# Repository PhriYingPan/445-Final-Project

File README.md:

# Desk Aid Learning Device 

### Team Members

- [Aidan Johnston](https://github.com/AidanJ16)
- [Conan Pan](https://github.com/PhriYingPan)
- [Ethan Ge](https://github.com/ethange2)

## 1.1 Problem

In recent years, there has been a growing trend of integrating technology into schools. This trend has been accelerated by the lasting impacts of the Covid-19 pandemic and the continuous advancements in digital devices and tools. Schools across the nation have adopted computers, tablets, and virtual learning platforms to enhance education and increase accessibility in the pursuit of modernizing the classroom. While these technologies offer incredible benefits, they also introduce challenges, particularly in elementary school classrooms. 

One of the most critical problems is the effect screen time is having on students. By incorporating technological devices in classrooms, students are spreading prolonged periods interacting with screens. Studies have begun to highlight how this excessive screen time can lead to a severe lack of social skills, shorter attention spans, and higher frequencies of disruptions. These trends contribute to a less effective and unhealthy learning environment. Furthermore, studies are exploring connections between prolonged exposure to screens and decreases in mental and physical well-being. Therefore, in the pursuit of generating a more social, engaging, and nurturing environment for young students we propose the desk learning aid device.

## 1.2 Solution

The desk learning aid device will function through various buttons and a scroller connected to a customized PCB device. These buttons and the scroller will correspond to responding to polls/questions, comprehension checks, asking questions, and more. The device will communicate to an application that can be monitored by the teacher where they will receive real-time feedback. The teacher can have a better understanding of the student’s comprehension levels and be able to properly cater towards providing the students the most effective lesson. The purpose of this device would be to provide a cost-effective solution that can be set up at each student’s desk to promote a stronger and healthier learning environment for students. This differs from other options on the market due to easier set up because other options require you to create a question in order to receive a response, however, our device allows for many passive inputs including comprehension and other urgent needs. In addition, other portable solutions require students to buy each device individually costing them hundreds of dollars, but our solution only requires the purchase of a reusable RFID keycard that is cheap and easy to use.

# Visual Aid 

# Results

 - [Demo Video](https://drive.google.com/file/d/13fJDIUi9QKVj2l2KASiBSuiVs_a9EkWj/view?usp=sharing)
 - [Presentation](https://github.com/user-attachments/files/20017662/Desk.Aid.Learning.Device.Team.27.pptx)
 - [Design Document](https://github.com/user-attachments/files/20017668/445.Design.Document.3.pdf)

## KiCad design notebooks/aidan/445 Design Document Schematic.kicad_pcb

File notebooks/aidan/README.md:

# Aidan Johnston's Lab Notebook – Desk Learning Aid Device

This notebook documents the comprehensive design, development, testing, and firmware implementation for the Desk Learning Aid Device. It particularly highlights my contributions to the customized PCB and subsystem integration.

---

## 2025-02-01 – Initial Project Direction

**Objectives:**

* Discussed the core project idea and goals with teammates and our TA, Kaiwen Cao.
* Explored engagement mechanisms suitable for classroom environments that avoid excessive screen time.

**Progress:**

* Proposed using a physical interaction system incorporating RFID-based student identification, button-based input, and a rotary encoder or potentiometer scroller.
* Envisioned a backend system supported by Firebase to relay data to a real-time web dashboard accessible to teachers.
* Sketched an initial block diagram representing all subsystems (power, microcontroller, interface, input, and RFID).

---

## 2025-02-14 – Finalize Project

**Objectives:**

* Solidify the overall architecture and prepare for the proposal review.

**Progress:**

* Finalized a refined block diagram detailing subsystem interactions.
* Designed initial device enclosures and mounting plans for discussion with the Machine Shop.
* Scheduled zoom meetings with elementary school teachers to ensure project alignment with classroom needs.
* Began outlining our project proposal for review by course instructors and TAs.

---

## 2025-02-23 – Initial PCB Design Part 1

**Objectives:**

* Begin translating conceptual design into manufacturable electronic schematics.

**Progress:**

* Created a rough draft schematic in KiCad featuring major components: ESP32-S3, push buttons, RFID, voltage regulators, and display interface.
* Assigned preliminary footprints to each component, focusing on pin mapping and layout constraints.

---

## 2025-03-05 – Initial PCB Design Part 2

**Objectives:**

* Convert schematic to a routed PCB design and initiate documentation.

**Progress:**

* Structured the PCB by subsystem (power, input, interface, RFID, microcontroller), allowing for intuitive routing.
* Assigned logical labels, visibility settings, and ground stitching to reduce EMI.
* Helped draft the design documentation section related to PCB layout, component selection, and routing decisions.

---

## 2025-03-13 – Initial PCB Design Part 3

**Objectives:**

* Submit the initial board to PCBWay.

**Progress:**

* Used KiCad's Design Rule Checker to identify and correct errors.
* Submitted and passed PCBWay's manufacturing audit.
* Submitted the design to our TA as apart of the Second Round Orders.

---

## 2025-03-24 – Updated PCB Design Part 1

**Objectives:**

* Evaluate prior board and fix discovered issues.

**Challenges:**

* Incorrect footprint for buck-boost converter (TPS63001).
* Programming circuit for ESP32-S3 not compatible with UART flashing.
* Incorrect footprints for push buttons, inverters, and LCD connector.

**Solutions:**

* Corrected all footprints by referencing datasheets and comparing to KiCad libraries.
* Revised programming method to use USB-to-UART dongle with GND, TX, RX, DTR, RTS lines.
* Rechecked layout and connections for consistency and ease of access.

---

## 2025-03-31 – Updated PCB Design Part 2

**Objectives:**

* Submit improved board design.

**Progress:**

* Rerouted traces and updated board labeling.
* Verified footprint clearances and pad sizes.
* Used KiCad's Design Rule Checker to identify and correct errors.
* Submitted and passed PCBWay's manufacturing audit.
* Submitted the design to our TA as apart of the Third Round Orders.

---

## 2025-04-17 – Hardware Testing

**Objectives:**

* Validate the power subsystem and ESP32 flashing.

**Progress:**

* Measured 3.27V at ESP32 input pin (target: 3.3V).
* Identified error in design: resistor R13 (pull-down) interfered with programming, removed it to enable successful flashing.

---

## 2025-04-29 – Software Testing

**Objectives:**

* Program LCD to verify interface subsystem.

**Progress:**

* Initial attempts to display characters failed.
* Identified reversed SPI pin assignments to LCD: MOSI needed to connect to SID, and MISO to SOD.
* Recognized need for external RST circuit for reliable LCD initialization.

---
## Verification Procedures

**1. DRC Testing**

* All boards verified using KiCad’s DRC.
* Ensured clearance, trace width, and via rules met manufacturing constraints.

**2. Continuity Testing**

* Verified pin-to-pin connections and ground continuity.
* Used multimeter beep function across all critical signal lines.

**3. Power Integrity Test**

* Verified output voltages at ESP32 (3.27V), LCD, and RFID reader.
* Measured battery charge and boost output stability under load.

**4. Boot and Flash Test**

* Helped successfully flash test program using esptool.py.

**5. Input Test**

* Button presses triggered correct GPIO interrupts.
* Potentiometer yielded stable ADC values.

---

## Bibliographic References

1. Espressif Systems. (2023). *ESP32-S3-WROOM-1 & ESP32-S3-WROOM-1U Datasheet*.
2. Firebase. (2024). *Realtime Database Documentation*.
3. ELECTRONIC ASSEMBLY GmbH. (n.d.). *DOGS104E Graphic Display Module*.
4. Texas Instruments. (2008). *TPS63000 High-Efficiency Buck-Boost Converter Datasheet*.
5. TOPPOWER. (2023). *TP4057 Battery Charging and Protection IC Datasheet*.
6. Texas Instruments. (2002). *SN74LS05 Hex Inverter Datasheet*.
7. NXP Semiconductors. (2018). *PN512 NFC Reader IC Datasheet*.
8. Adafruit. (n.d.). *Push Button #492*.
9. Bourns Inc. (2020). *PDB181 Series Potentiometer Datasheet*.
10. IEEE. (2023). *IEEE Code of Ethics*.
11. U8G2 Library Documentation. (2024). *Monochrome Graphics Library for Embedded Devices*.

---

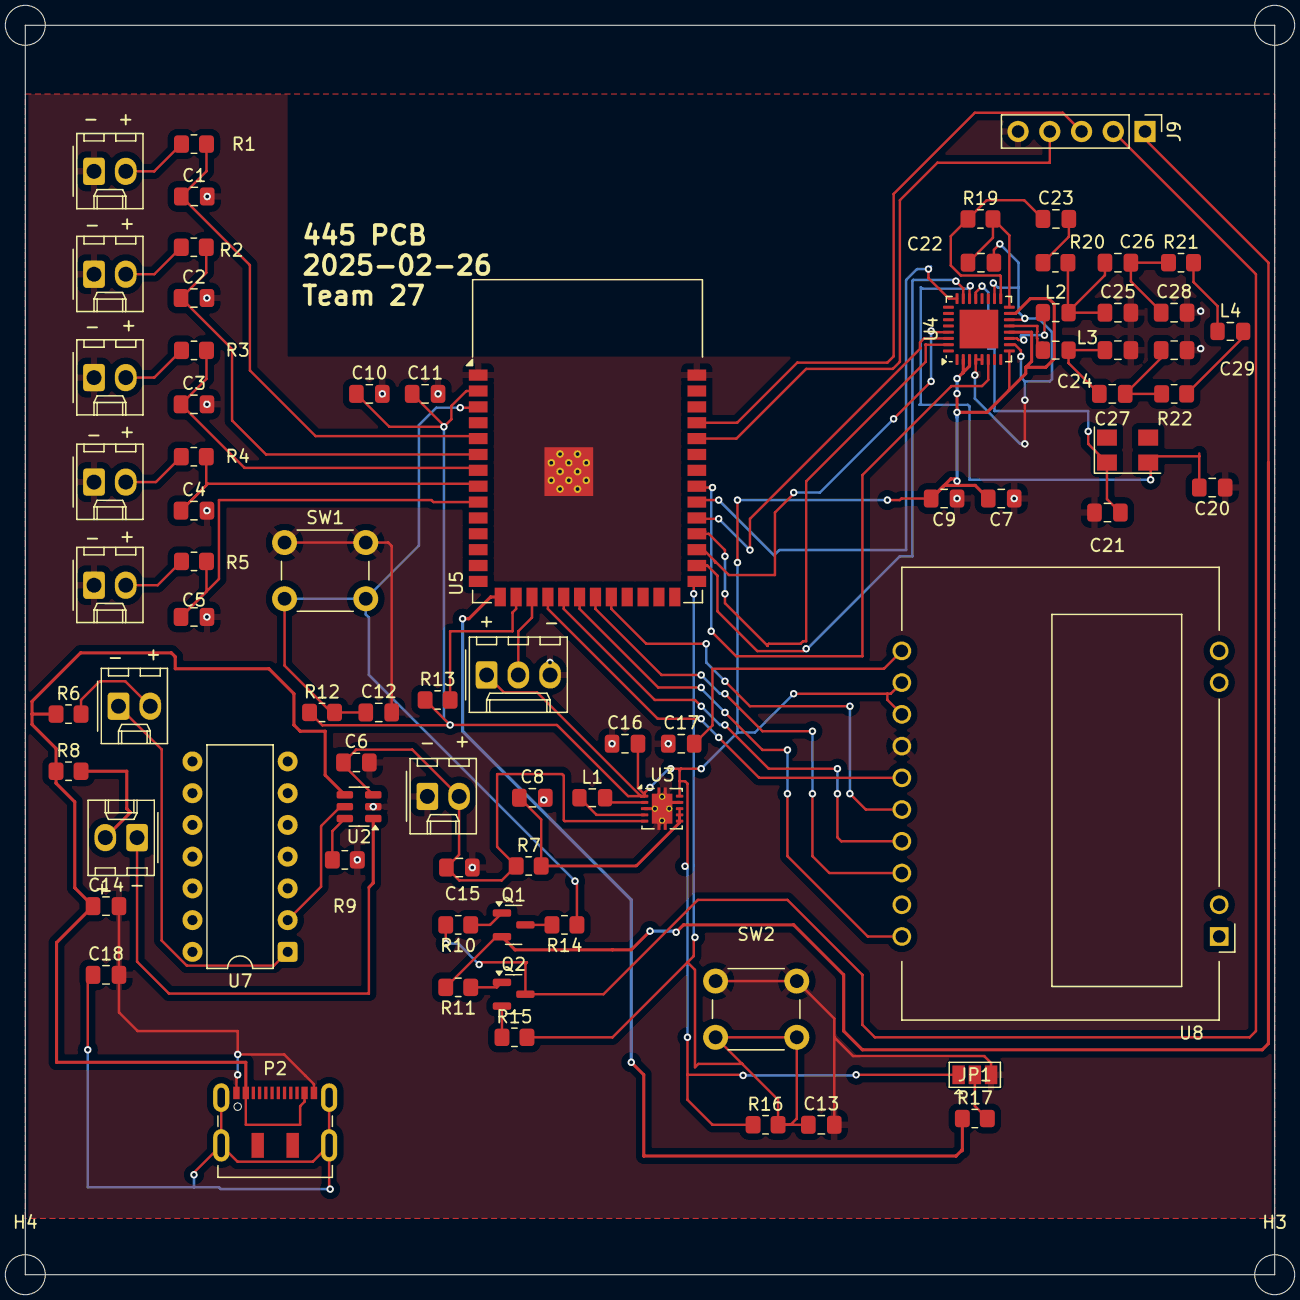
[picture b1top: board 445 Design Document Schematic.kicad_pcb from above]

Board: 2 copper layers, 100.0 x 100.0 mm, 80 parts (0 on the bottom side), 63 nets.

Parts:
C1, C2, C3, C4, C5, C12, C13, C14, C16, C17: 1uF; C_0805_2012Metric_Pad1.18x1.45mm_HandSolder
C6, C7, C10, C15, C18: 10uF; C_0805_2012Metric_Pad1.18x1.45mm_HandSolder
C8: 0.1uF; C_0805_2012Metric_Pad1.18x1.45mm_HandSolder
C9: 100nF; C_0805_2012Metric_Pad1.18x1.45mm_HandSolder
C11, C22, C23, C26, C27, C28, C29: 0.01uF; C_0805_2012Metric_Pad1.18x1.45mm_HandSolder
C20, C21, C24, C25: 0.001uF; C_0805_2012Metric_Pad1.18x1.45mm_HandSolder
D1, D2: LED; Molex_KK-254_AE-6410-02A_1x02_P2.54mm_Vertical
H1, H2, H3, H4: MountingHole; MountingHole_3.2mm_M3
J1, J2, J3, J4, J5: BUTTON; Molex_KK-254_AE-6410-02A_1x02_P2.54mm_Vertical
J6: POT; Molex_KK-254_AE-6410-03A_1x03_P2.54mm_Vertical
J7: LiPo Battery; Molex_KK-254_AE-6410-02A_1x02_P2.54mm_Vertical
J9: Conn_01x05_Socket; PinHeader_1x05_P2.54mm_Vertical
JP1: SolderJumper_3_Open; SolderJumper-3_P1.3mm_Open_Pad1.0x1.5mm
L1, L2, L3, L4: 2.2uH; L_0805_2012Metric_Pad1.15x1.40mm_HandSolder
P2: USB_C_Plug; USB_C_Receptacle_JAE_DX07S016JA1R1500
Q1, Q2: SS8050; SOT-23
R1, R2, R3, R4, R5, R10, R11, R14, R15, R19, R20: 10k; R_0805_2012Metric_Pad1.20x1.40mm_HandSolder
R6, R8: 330; R_0805_2012Metric_Pad1.20x1.40mm_HandSolder
R7: 0.1k; R_0805_2012Metric_Pad1.20x1.40mm_HandSolder
R9: 2k; R_0805_2012Metric_Pad1.20x1.40mm_HandSolder
R12, R16: 100k; R_0805_2012Metric_Pad1.20x1.40mm_HandSolder
R13, R17: 1k; R_0805_2012Metric_Pad1.20x1.40mm_HandSolder
R21, R22: 100; R_0805_2012Metric_Pad1.20x1.40mm_HandSolder
SW1, SW2: SW_Push; SW_PUSH_6mm
U2: Charge Station; TSOT-23-6
U3: Converter; Texas_DRC0010J_ThermalVias
U4: PN5120A0HN1 RFID; HVQFN-32-1EP_5x5mm_P0.5mm_EP3.1x3.1mm
U5: ESP32-S3-WROOM-1
U7: Inverter; DIP-14_W7.62mm
U8: EA_DOGS104B-A; EA_DOGS104X-A
Y1: 27.12MHz; Crystal_SMD_5032-4Pin_5.0x3.2mm

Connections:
+3.3V: C7.2, C9.2, C10.1, C11.1, C16.2, J6.1, JP1.1 (A), R12.1, R13.1, R16.1, U3.1 (VOUT), U3.10 (FB), U4.2 (PVDD), U4.3 (DVDD), U4.9 (SVDD), U4.12 (TVDD), U4.15 (AVDD), U5.2 (3V3), U8.12 (IM1), U8.13 (VDD)
+5V: C6.1, C15.1, J7.2, R7.1, U2.3 (BAT), U3.5 (VIN)
/Button_1: C1.1, R1.1, U5.5 (IO5)
/Button_2: C2.1, R2.1, U5.6 (IO6)
/Button_3: C3.1, R3.1, U5.7 (IO7)
/Button_4: C4.1, R4.1, U5.8 (IO15)
/Button_5: C5.1, R5.1, U5.9 (IO16)
/CHIP_PU: C12.1, R12.2, R14.1, SW1.2, U5.3 (EN)
/DTR: J9.2, Q2.3 (C), R10.2
/Display_CS: U5.21 (IO13), U8.18 (~CS)
/Display_MISO: U5.22 (IO14), U8.16 (SID)
/Display_MOSI: U5.18 (IO10), U8.15 (SOD)
/Display_RST: U5.20 (IO12), U8.20 (~RST)
/Display_SCLK: U5.19 (IO11), U8.17 (SCLK)
/GPIO0_STRAPPING: C13.1, R15.2, R16.2, SW2.2, U5.27 (IO0)
/GPIO3_STRAPPING: R17.1, U5.15 (IO3)
/GPIO46_STRAPPING: R13.2, U5.16 (IO46)
/POT: J6.2, U5.17 (IO9)
/RFID_CS: U4.24 (ALE), U5.32 (IO39)
/RFID_IRQ: U4.23 (IRQ), U5.28 (IO35)
/RFID_MISO: U4.31 (D7), U5.30 (IO37)
/RFID_MOSI: U4.30 (D6), U5.31 (IO38)
/RFID_RST: U4.6 (~NRSTPD), U5.33 (IO40)
/RFID_SCK: U4.29 (D5), U5.29 (IO36)
/RTS: J9.1, Q1.2 (E), R11.2
/RX: J9.4, U5.36 (RXD0)
/TX: J9.3, U5.37 (TXD0)
GND: C1.2, C2.2, C3.2, C4.2, C5.2, C6.2, C7.1, C8.2, C9.1, C10.2, C11.2, C12.2, C13.2, C14.2, C15.2, C16.1, C17.1, C18.2, C20.1, C21.1, C22.2, C24.1, C25.2, C28.2, C29.1, J1.1, J2.1, J3.1, J4.1, J5.1, J6.3, J7.1, J9.5, JP1.3 (B), P2.A1 (GND), P2.A12 (GND), P2.B1 (GND), P2.B12 (GND), R9.2, SW1.1, SW2.1, U2.2 (GND), U3.3 (PGND), U3.9 (GND), U3.11 (PGND), U4.4 (DVSS), U4.5 (PVSS), U4.10 (TVSS), U4.14 (TVSS), U4.18 (AVSS), U5.1 (GND), U5.40 (GND), U5.41 (GND), U8.14 (VSS)
unnamed: C23.2, R20.1
unnamed: C24.2, C27.1, L3.2
unnamed: C25.1, C26.1, L2.2, R20.2
unnamed: C26.2, C28.1, R21.1
unnamed: C27.2, C29.2, R22.1
unnamed: D1.2 (A), R6.2
unnamed: D1.1 (K), U7.1
unnamed: D2.2 (A), R8.2
unnamed: D2.1 (K), U2.1 (~CHRG)
unnamed: J1.2, R1.2
unnamed: J2.2, R2.2
unnamed: J3.2, R3.2
unnamed: J4.2, R4.2
unnamed: J5.2, R5.2
unnamed: JP1.2 (C), R17.2
unnamed: L4.1, R21.2
unnamed: L4.2, R22.2
unnamed: C18.1, P2.S1 (SHIELD)
unnamed: Q1.1 (B), R10.1
unnamed: Q1.3 (C), R14.2
unnamed: Q2.1 (B), R11.1
unnamed: Q2.2 (E), R15.1
unnamed: R9.1, U2.6 (PROG)
unnamed: U2.5 (STDBY), U7.2
unnamed: C14.1, P2.A4 (VBUS), P2.A9 (VBUS), P2.B4 (VBUS), P2.B9 (VBUS), R6.1, R8.1, U2.4 (V_{CC})
unnamed: C8.1, R7.2, U3.6 (EN), U3.7 (PS/SYNC), U3.8 (VINA)
unnamed: L1.1, U3.4 (L1)
unnamed: L1.2, U3.2 (L2)
unnamed: C21.2, U4.21 (OSCIN), Y1.1
unnamed: C20.2, U4.22 (OSCOUT), Y1.2
unnamed: C23.1, R19.1, U4.17 (RX)
unnamed: L2.1, U4.11 (TX1)
unnamed: L3.1, U4.13 (TX2)
unnamed: C22.1, R19.2, U4.16 (VMID)
unnamed: C17.2, U8.11 (VOUT)

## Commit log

2025-03-04 Update README.md with schedule
2025-04-03 Prototype webapp using dummy data
2025-04-12 added backend that can send a recieve dummy data to firebase using wifi
2025-04-12 storing backup code
2025-04-12 removing
2025-04-23 buttons and pot working
2025-04-24 new code commented out u8g2 logic
2025-04-24 adding raise hand
2025-05-02 creating new folder
2025-05-02 adding dummy folders
2025-05-02 adding images
